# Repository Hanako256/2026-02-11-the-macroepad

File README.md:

# The Macroepad
The Macroepad is a macropad with 6 keys, 3 poe drawings on the PCB, and very intentional spelling. It is my first ever hardware project.

## PCB + Schematic
### Schematic:

### PCB:

I don't even know how many times I redesigned this part...from just changing the wiring to restarting from scratch, it must have gone through over 7 versions by now, but I'm finally happy with this.

2 of those poes will never see the light of day...oh well, sacrifices must be made.

## Case

Made in Onshape. As a result of the pcb redesigning, this case has also been redesigned and re-exported far too many times. [Onshape document](https://cad.onshape.com/documents/2e1ab0f3adffe5da9127a695/w/749a84079cf19a1d14ae1bdd/e/1d03814740b6b7ee83d894f7)

## Firmware
The Macroepad uses KMK firmware. 4 of the 6 keys are directional inputs (like arrow keys on a regular keyboard), the other 2 are for Right Click and Enter.

## BOM
6x Cherry MX Switches

1x Seeed XIAO RP2040

6x DSA Keycaps

4x M3x16mm Screws

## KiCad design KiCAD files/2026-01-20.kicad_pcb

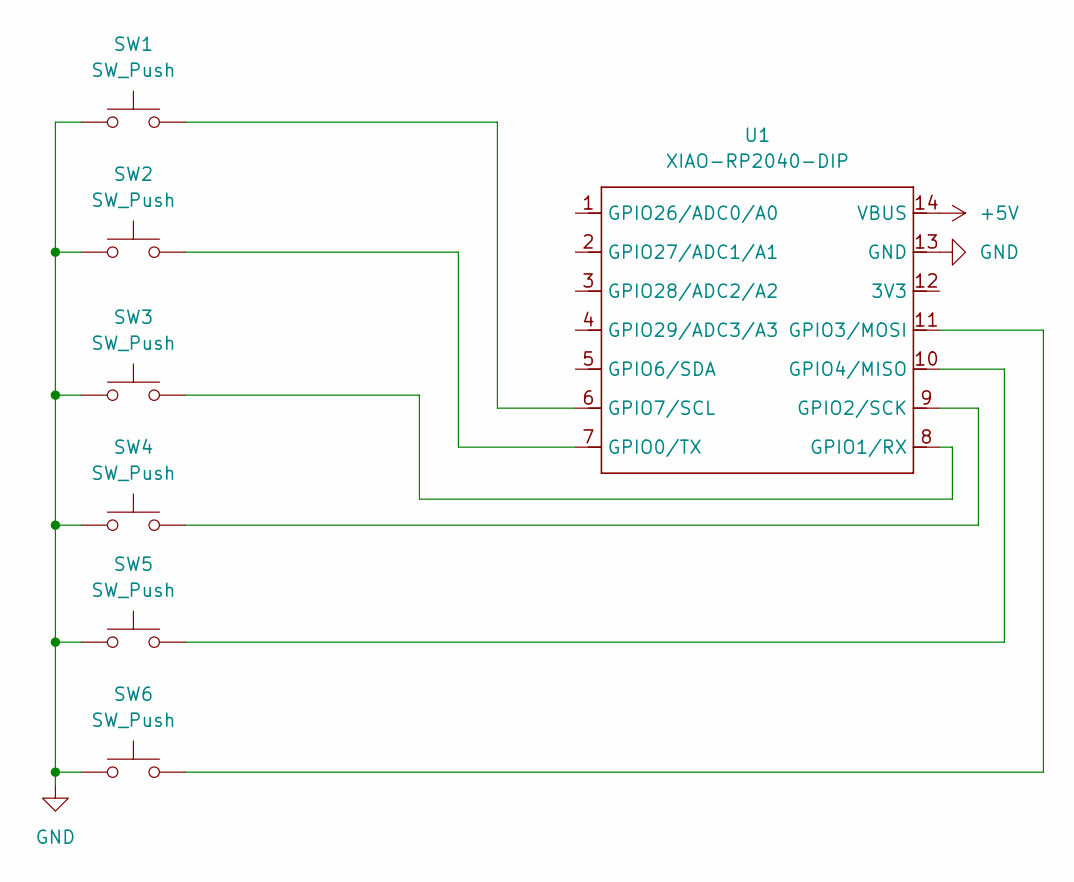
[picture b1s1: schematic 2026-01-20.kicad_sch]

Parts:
SW1, SW2, SW3, SW4, SW5, SW6: SW_Push; SW_Cherry_MX_1.00u_PCB
U1: XIAO-RP2040-DIP

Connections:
+5V: U1.14 (VBUS)
GND: SW1.1, SW2.1, SW3.1, SW4.1, SW5.1, SW6.1, U1.13 (GND)
unnamed: SW2.2, U1.7 (GPIO0/TX)
unnamed: SW3.2, U1.8 (GPIO1/RX)
unnamed: SW4.2, U1.9 (GPIO2/SCK)
unnamed: SW6.2, U1.11 (GPIO3/MOSI)
unnamed: SW5.2, U1.10 (GPIO4/MISO)
unnamed: SW1.2, U1.6 (GPIO7/SCL)

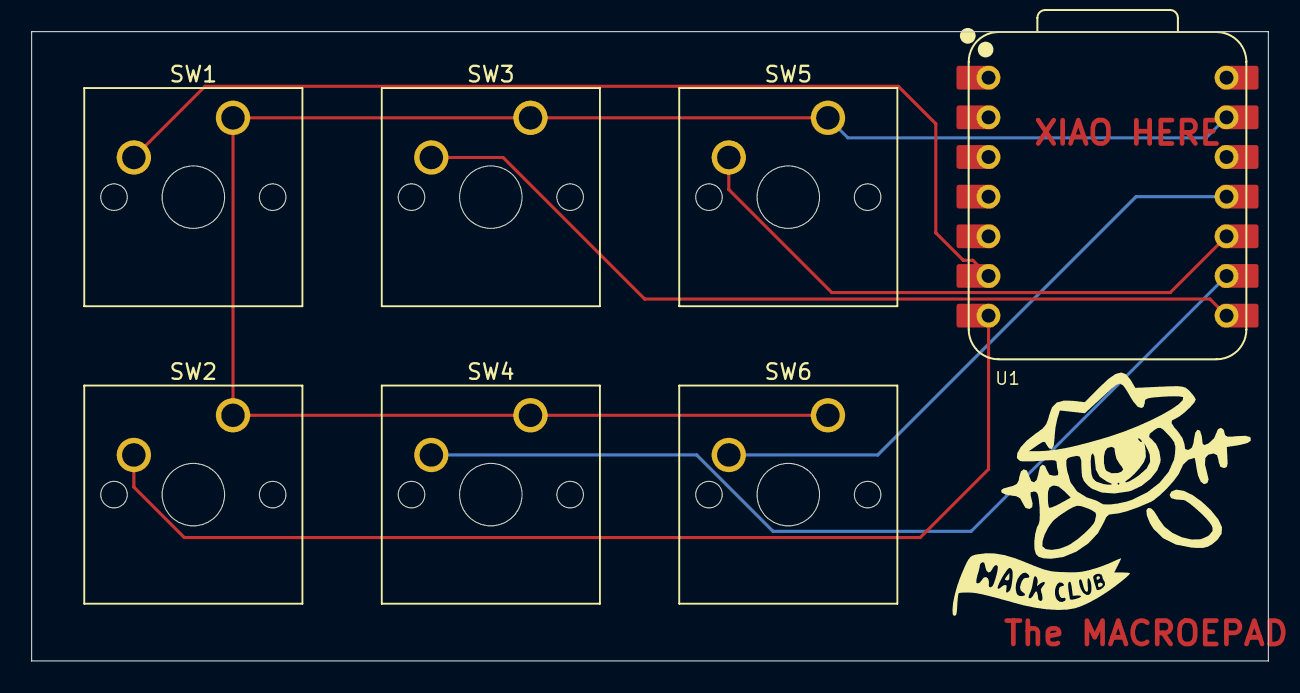
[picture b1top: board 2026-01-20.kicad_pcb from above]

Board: 2 copper layers, 79.2 x 40.3 mm, 7 parts (0 on the bottom side), 7 nets.

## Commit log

2026-02-12 moved files to repo
2026-02-12 organized files better
2026-02-12 changed some files around
2026-02-13 re-exported the CAD model and added some images
2026-02-21 added drill files to gerbers
